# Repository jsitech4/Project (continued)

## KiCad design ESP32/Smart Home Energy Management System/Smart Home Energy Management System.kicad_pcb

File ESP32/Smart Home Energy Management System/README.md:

# Smart Home Energy Management System
Generated using KiCad Industrial Setup Script

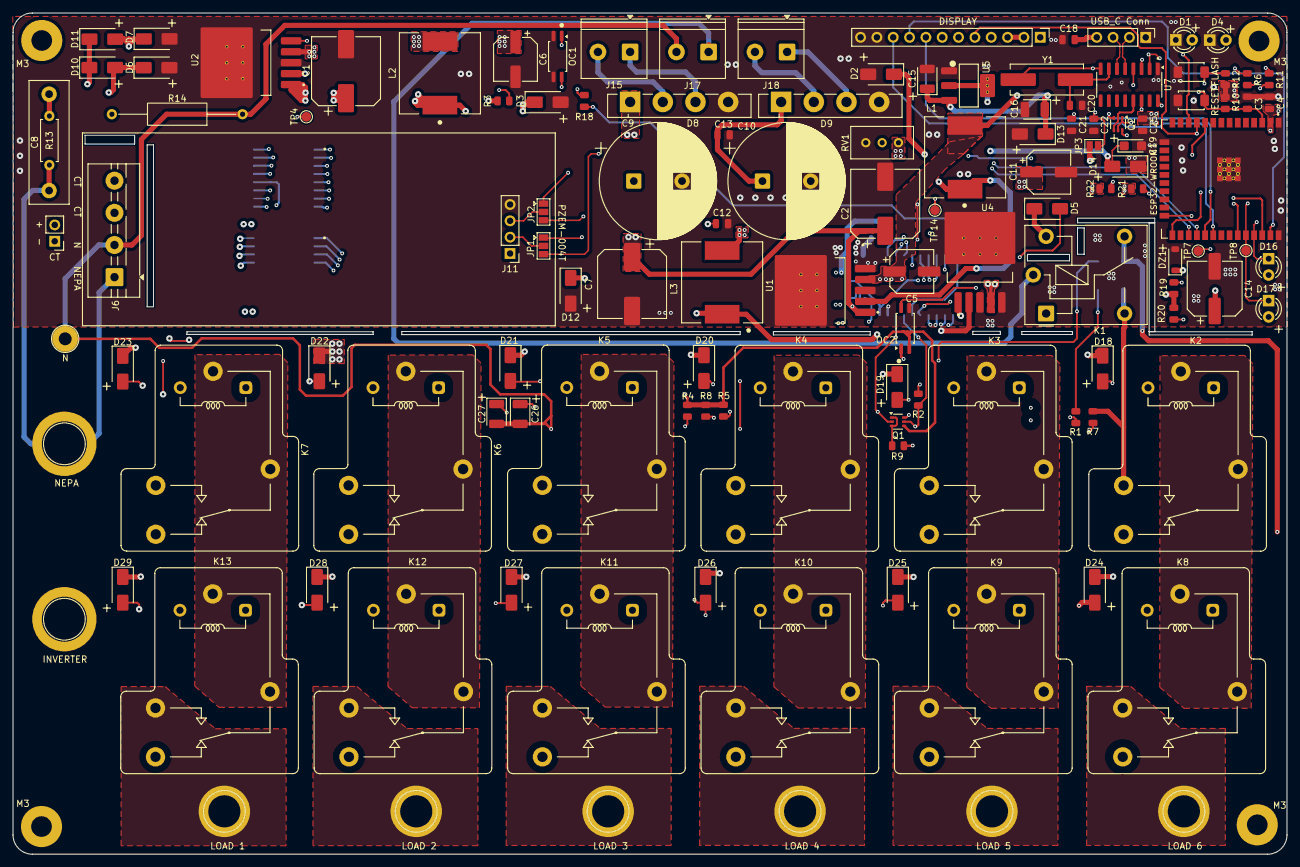
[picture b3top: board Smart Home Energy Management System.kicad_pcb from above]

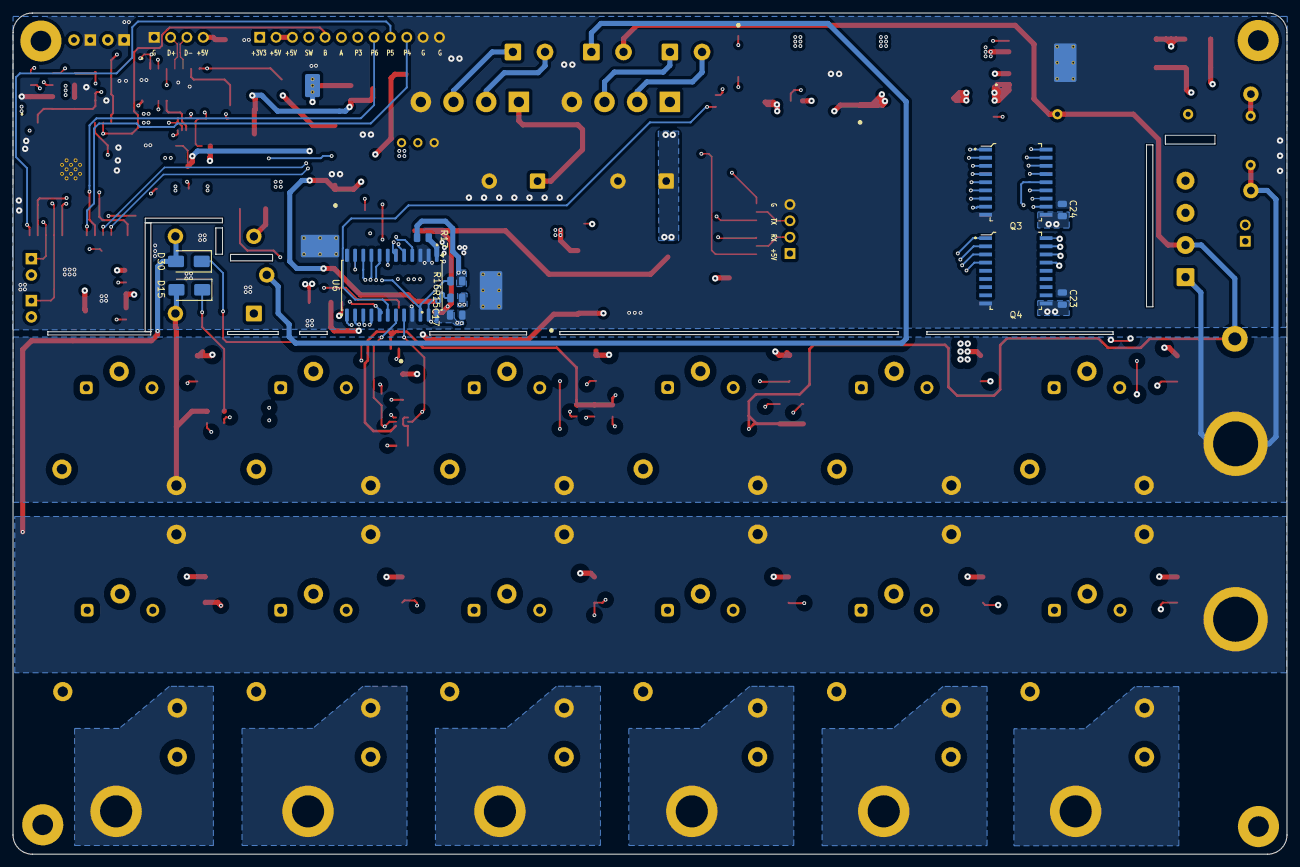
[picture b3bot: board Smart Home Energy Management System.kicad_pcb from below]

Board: 4 copper layers, 198.1 x 130.8 mm, 137 parts (11 on the bottom side), 102 nets.

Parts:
C1, C2, C7: 680uF_35V; CP_Elec_10x12.5
C3: 470nF; C_0805
C4, C12, C13, C18, C22, C23, C24, C25: 100nF; C_0805
C5, C6, C11: 220uF_16V; CP_Elec_6.3x7.7
C8: 145J400V; C_Rect_L19.0mm_W6.0mm_P15.00mm_MKS4
C9, C10: 2200uF/35V; CP_Radial_D18.0mm_P7.50mm
C14: 470uF/25V; CP_Elec_8x11.9
C15: 4.7uF/16V; C_CASE-B-3528-21(mm)
C16, C26, C27: 10uF_16V; C_CASE-B-3528-21(mm)
C17: 0.1uF/25V; C_0805
C19: 4.7uF/16V; CP_EIA-3216-18_Kemet-A
C20, C21: 22pF; C_0805
D1: Blue; LED_D3.0mm
D2, D3, D12: 1N5824; D_SMA
D4: GREEN; LED_D3.0mm
D5, D6, D7, D10, D11, D18, D19, D20, D21, D22, D23, D24, D25, D26, D27, D28, D29: SM4001; D_SMA
D8, D9: GBU8M; Diode_Bridge_Vishay_GBU
D13, D14: 1N5819; D_SMA
D15, D30: SM4007PL; D_SMA
D16: Red; LED_D3.0mm
D17: Green; LED_D3.0mm
DZ1: CMZ12; D_SOD-123
J1: NEPA; TestPoint_Plated_Hole_D5.0mm
J2: INVERTER; TestPoint_Plated_Hole_D5.0mm
J3: CT; PinHeader_1x02_P2.54mm_Vertical
J6: PZEM_LOAD; TerminalBlock_MaiXu_MX126-5.0-04P_1x04_P5.00mm
J10: N; TestPoint_Plated_Hole_D5.0mm
J11: PZEM_SIG; PinHeader_1x04_P2.54mm_Vertical
J14: USB_C Conn; PinHeader_1x04_P2.54mm_Vertical
J15: TRANS 1-OUT; TerminalBlock_Phoenix_PT-1,5-2-5.0-H_1x02_P5.00mm_Horizontal
J17: TRANS-IN; TerminalBlock_Phoenix_PT-1,5-2-5.0-H_1x02_P5.00mm_Horizontal
J18: TRANS 2-OUT; TerminalBlock_Phoenix_PT-1,5-2-5.0-H_1x02_P5.00mm_Horizontal
J19: DISPLAY; PinHeader_1x12_P2.54mm_Vertical
J20: LOAD 6; TestPoint_Plated_Hole_D5.0mm
J21: LOAD 5; TestPoint_Plated_Hole_D5.0mm
J22: LOAD 4; TestPoint_Plated_Hole_D5.0mm
J23: LOAD 3; TestPoint_Plated_Hole_D5.0mm
J24: LOAD 2; TestPoint_Plated_Hole_D5.0mm
J25: LOAD 1; TestPoint_Plated_Hole_D5.0mm
JP1, JP2: SolderJumper-3_P1.3mm_Open_Pad1.0x1.5mm
JP3: SolderJumper-2_P1.3mm_Open_Pad1.0x1.5mm
K1: 10A RELAY; Relay_SPDT_Finder_36.11
K2, K3, K4, K5, K6, K7, K8, K9, K10, K11, K12, K13: 30A RELAY; Relay_SPDT_RAYEX-L90
L1, L2, L3: 33uH; L_12x12mm_H6mm
OC1, OC2: PC817XFP; SOP-4_4.4x2.6mm_P1.27mm
Q1, Q2: UMH3N; SOT-363_SC-70-6
Q3, Q4: ULN2803ADWR; SOIC-18_W7.5mm
R1, R2, R7: 680k; R_0805
R3: 100k; R_0805
R4, R5, R8: 6.8k; R_0805
R6, R9, R11, R19, R20: 330R; R_0805
R10, R12, R15, R16, R17, R21, R22: 10k; R_0805
R13: 1M; R_Axial_DIN0207_L6.3mm_D2.5mm_P7.62mm_Horizontal
R14: 330R/2W; R_Axial_DIN0309_L9.0mm_D3.2mm_P20.32mm_Horizontal
R18: 150R; R_0805
RV1: 10K; Potentiometer_Bourns_3296W_Vertical
SW1: RESET; SW_TS-1088-AR02016
SW2: FLASH; SW_TS-1088-AR02016
TP4, TP7, TP8, TP14: TestPoint; TestPoint_Pad_D1.5mm
U1: LM2596S-3.3V; TO-263-5_L10.2-W8.9-P1.70-TL
U2: LM2596S-12; TO-263-5_L10.2-W8.9-P1.70-TL
U3: ESP32-WROOM; ESP32-WROOM-32E
U4: LM2596S-5V; TO-263-5_L10.2-W8.9-P1.70-TL
U5: AMS1117-3.3; SOT-223-3_L6.5-W3.4-P2.30-LS7.0-BR
U6: PCA9555D; SOIC-24W_7.5x15.4mm_P1.27mm
U7: CH340C; SOIC-16_3.9x9.9mm_P1.27mm
Y1: 12MHz; CRYSTAL-SMD_L11.5-W4.8-LS12.7

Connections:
+3.3V: C4.2, C5.1, C17.1, C25.2, D14.1 (K), J19.1, JP3.2 (B), L1.2, R10.2, R12.2, R15.2, R16.2, R17.2, R19.1, R20.1, R21.2, R22.1, U1.4 (FB), U3.2 (VDD), U6.24 (VDD), U7.16 (VCC)
+5V: C11.1, J11.1, J19.2, J19.3, L3.2, RV1.3, U4.4 (FB)
+12V: C6.1, C23.1, C24.1, D18.1 (K), D19.1 (K), D20.1 (K), D21.1 (K), D22.1 (K), D23.1 (K), D24.1 (K), D25.1 (K), D26.1 (K), D27.1 (K), D28.1 (K), D29.1 (K), K2.A1, K3.A1, K4.A1, K5.A1, K6.A1, K7.A1, K8.A2, K9.A2, K10.A2, K11.A2, K12.A2, K13.A2, L2.2, Q3.10 (COM), Q4.10 (COM), U2.4 (FB)
/1TR 1: D8.3, J15.1
/1TR 2: D8.2, J15.2
/2TR 1: D9.3, J18.1
/2TR 2: D9.2, J18.2
/12V_EN: OC1.1, R18.1
/CONST: J19.7, RV1.2
/CT +: J3.2, J6.4
/CT -: J3.1, J6.3
/D+: J14.2, U7.5 (UD+)
/D-: J14.3, U7.6 (UD-)
/DTR: Q2.2 (B1), Q2.4 (E2), U7.13 (~DTR)
/EN: C3.2, Q2.6 (C1), R10.1, SW1.2, U3.3 (EN)
/GPIO0: Q2.3 (C2), R12.1, SW2.2, U3.25 (IOA0)
/GPIO1/TX: D16.1 (K), JP1.1 (A), TP7.1, U3.35 (TXD0/IO1), U7.3 (RXD)
/GPIO2: R11.1, U3.24 (IOA2)
/GPIO3/RX: D17.1 (K), JP2.3 (C), TP8.1, U3.34 (RXD0/IO3), U7.2 (TXD)
/GPIO5/CS: J19.8, U3.29 (IO5)
/GPIO16: JP2.1 (A), U3.27 (IO16)
/GPIO17: JP1.3 (C), U3.28 (IO17)
/GPIO18/SCK: J19.10, U3.30 (IO18)
/GPIO21/SDA: R15.1, U3.33 (IO21), U6.23 (SDA)
/GPIO22/SCL: R16.1, TP14.1, U3.36 (IO22), U6.22 (SCL)
/GPIO23/MOSI: J19.9, U3.37 (IO23)
/GPIO25: J19.6, R22.2, U3.10 (IOA25)
/GPIO26: J19.5, R21.1, U3.11 (IOA26)
/GPIO27: J19.4, U3.12 (IOA27)
/IND_LED: R6.1, U6.17 (IO1_4)
/INVERTER: D30.2 (A), J2.1, K1.12, K2.12, K3.12, K4.12, K5.12, K6.12, K7.12
/INVERTER_SENSE: C27.1, Q1.5 (B2), R2.1, R4.2, U6.19 (IO1_6)
/LOAD1: J25.1, K13.14
/LOAD2: J24.1, K12.14
/LOAD3: J23.1, K11.14
/LOAD4: J22.1, K10.14
/LOAD5: J21.1, K9.14
/LOAD6: J20.1, K8.14
/N: C26.2, C27.2, J6.2, J10.1, J17.2, OC2.2, Q1.4 (E2), R4.1, R5.1, R8.1, R14.1
/NEPA: C8.2, D15.2 (A), J1.1, J6.1, K1.14, K2.14, K3.14, K4.14, K5.14, K6.14, K7.14, R7.2, R13.2
/NEPA_SENSE: C26.1, Q1.2 (B1), R1.1, R5.2, U6.20 (IO1_7)
/RD1C1: D24.2 (A), K8.A1, Q3.18 (OUT1)
/RD1C2: D18.2 (A), K2.A2, Q3.17 (OUT2)
/RD1C3: D25.2 (A), K9.A1, Q3.16 (OUT3)
/RD1C4: D19.2 (A), K3.A2, Q3.15 (OUT4)
/RD1C5: D26.2 (A), K10.A1, Q3.14 (OUT5)
/RD1C6: D20.2 (A), K4.A2, Q3.13 (OUT6)
/RD1C7: D27.2 (A), K11.A1, Q3.12 (OUT7)
/RD1C8: D21.2 (A), K5.A2, Q3.11 (OUT8)
/RD2C1: D28.2 (A), K12.A1, Q4.18 (OUT1)
/RD2C2: D22.2 (A), K6.A2, Q4.17 (OUT2)
/RD2C3: D29.2 (A), K13.A1, Q4.16 (OUT3)
/RD2C4: D23.2 (A), K7.A2, Q4.15 (OUT4)
/RTS: Q2.1 (E1), Q2.5 (B2), U7.14 (~RTS)
/SELECT1: K7.11A, K7.11B, K13.11A, K13.11B
/SELECT2: K6.11A, K6.11B, K12.11A, K12.11B
/SELECT3: K5.11A, K5.11B, K11.11A, K11.11B
/SELECT4: K4.11A, K4.11B, K10.11A, K10.11B
/SELECT5: K3.11A, K3.11B, K9.11A, K9.11B
/SELECT6: K2.11A, K2.11B, K8.11A, K8.11B
/TRANS-IN: J17.1, K1.11
/~INT: R17.1, U6.1 (~INT)
GND: C1.2, C2.2, C3.1, C4.1, C5.2, C6.2, C7.2, C9.2, C10.2, C11.2, C12.1, C13.1, C14.2, C15.2, C16.2, C17.2, C18.1, C19.2, C20.2, C21.2, C22.1, C23.2, C24.2, C25.1, D1.1 (K), D2.2 (A), D3.2 (A), D4.1 (K), D6.2 (A), D7.2 (A), D8.4 (-), D9.4 (-), D12.2 (A), D13.2 (A), DZ1.2 (A), J11.4, J14.1, J19.11, J19.12, OC1.2, OC1.3, OC2.3, Q3.9 (GND), Q4.9 (GND), RV1.1, SW1.1, SW2.1, U1.3 (GND), U1.5 (~ON/OFF), U1.6 (GND), U2.3 (GND), U2.6 (GND), U3.1 (GND), U3.15 (GND), U3.38 (GND), U3.39 (GND), U4.3 (GND), U4.5 (~ON/OFF), U4.6 (GND), U5.1 (GND), U6.2 (A1), U6.3 (A2), U6.12 (VSS), U6.21 (A0), U7.1 (GND)
unnamed: D1.2 (A), R6.2
unnamed: D2.1 (K), L1.1, U1.2 (OUT)
unnamed: D3.1 (K), L2.1, U2.2 (OUT)
unnamed: D4.2 (A), R11.2
unnamed: D5.2 (A), K1.A1, OC2.4
unnamed: C8.1, D6.1 (K), D10.2 (A), R13.1
unnamed: D7.1 (K), D11.2 (A), R14.2
unnamed: D12.1 (K), L3.1, U4.2 (OUT)
unnamed: C15.1, C16.1, C18.2, D13.1 (K), J14.4, U5.3 (VI)
unnamed: C19.1, D14.2 (A), U5.2 (VO), U5.4 (VO)
unnamed: D15.1 (K), R1.2
unnamed: D16.2 (A), R19.2
unnamed: D17.2 (A), R20.2
unnamed: D30.1 (K), R2.2
unnamed: J11.2, JP1.2 (B)
unnamed: J11.3, JP2.2 (B)
unnamed: C22.2, JP3.1 (A), U7.4 (V3)
unnamed: OC2.1, R9.2
unnamed: Q1.6 (C1), R7.1, R8.2
unnamed: Q1.1 (E1), Q1.3 (C2), R9.1
unnamed: Q3.1 (IN1), U6.4 (IO0_0)
unnamed: Q3.2 (IN2), U6.5 (IO0_1)
unnamed: Q3.3 (IN3), U6.6 (IO0_2)
unnamed: Q3.4 (IN4), U6.7 (IO0_3)
unnamed: Q3.5 (IN5), U6.8 (IO0_4)
unnamed: Q3.6 (IN6), U6.9 (IO0_5)
unnamed: Q3.7 (IN7), U6.10 (IO0_6)
unnamed: Q3.8 (IN8), U6.11 (IO0_7)
unnamed: Q4.1 (IN1), U6.13 (IO1_0)
unnamed: Q4.2 (IN2), U6.14 (IO1_1)
unnamed: Q4.3 (IN3), U6.15 (IO1_2)
unnamed: Q4.4 (IN4), U6.16 (IO1_3)
unnamed: OC1.4, R3.1, TP4.1, U2.5 (~ON/OFF)
unnamed: R18.2, U6.18 (IO1_5)
unnamed: C20.1, U7.7 (Xi), Y1.2
unnamed: C21.1, U7.8 (Xo), Y1.1
VCC1: C2.1, C7.1, C9.1, C12.2, D8.1 (+), U1.1 (VIN), U4.1 (VIN)
VCC2: C1.1, C10.1, C13.2, D9.1 (+), R3.2, U2.1 (VIN)
VCC3: C14.1, D5.1 (K), D10.1 (K), D11.1 (K), DZ1.1 (K), K1.A2

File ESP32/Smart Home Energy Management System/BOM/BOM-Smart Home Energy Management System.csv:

Comment,Designator,Footprint,LCSC,Quantity
ESP32,U3,ESP32-WROOM-32E,,1
LM2596S-12,U2,TO-263-5_L10.2-W8.9-P1.70-TL,,1
LM2596S-3.3V,U1,TO-263-5_L10.2-W8.9-P1.70-TL,,1
LM2596S-5V,U4,TO-263-5_L10.2-W8.9-P1.70-TL,,1
PCA9555D,U6,SOIC-24W_7.5x15.4mm_P1.27mm,,1
CH340C,U7,SOIC-16_3.9x9.9mm_P1.27mm,,1
ULN2803ADWR,Q4,SOIC-18_W7.5mm,,1
ULN2803ADWR,Q3,SOIC-18_W7.5mm,,1
680uF_35V,C1,CP_Elec_10x12.5,,1
6.8k,R5,R_0805,,1
Green,D17,LED_D3.0mm,,1
330R,R19,R_0805,,1
22pF,C21,C_0805,,1
GREEN,D4,LED_D3.0mm,,1
22pF,C20,C_0805,,1
470uF/25V,C14,CP_Elec_8x11.9,,1
4.7uF/16V,C15,C_CASE-B-3528-21(mm),,1
100nF,C4,C_0805,,1
100nF,C13,C_0805,,1
680k,R1,R_0805,,1
UMH3N,Q2,SOT-363_SC-70-6,,1
4.7uF/16V,C19,CP_EIA-3216-18_Kemet-A,,1
SM4001,D6,D_SMA,,1
145J400V,C8,C_Rect_L19.0mm_W6.0mm_P15.00mm_MKS4,,1
10uF_16V,C27,C_CASE-B-3528-21(mm),,1
PC817XFP,OC2,SOP-4_4.4x2.6mm_P1.27mm,,1
PC817XFP,OC1,SOP-4_4.4x2.6mm_P1.27mm,,1
150R,R18,R_0805,,1
SM4001,D20,D_SMA,,1
1N5824,D2,D_SMA,,1
330R,R20,R_0805,,1
330R/2W,R14,R_Axial_DIN0309_L9.0mm_D3.2mm_P20.32mm_Horizontal,,1
1N5819,D14,D_SMA,,1
SM4001,D29,D_SMA,,1
470nF,C3,C_0805,,1
10uF_16V,C26,C_CASE-B-3528-21(mm),,1
SM4001,D10,D_SMA,,1
SM4001,D23,D_SMA,,1
330R,R11,R_0805,,1
SM4001,D18,D_SMA,,1
SM4001,D21,D_SMA,,1
Blue,D1,LED_D3.0mm,,1
SM4001,D26,D_SMA,,1
33uH,L2,L_12x12mm_H6mm,,1
100nF,C25,C_0805,,1
SM4001,D24,D_SMA,,1
220uF_16V,C11,CP_Elec_6.3x7.7,,1
GBU8M,D9,Diode_Bridge_Vishay_GBU,,1
2200uF/35V,C9,CP_Radial_D18.0mm_P7.50mm,,1
SM4001,D19,D_SMA,,1
SM4001,D11,D_SMA,,1
1N5824,D12,D_SMA,,1
SM4001,D28,D_SMA,,1
6.8k,R4,R_0805,,1
SM4001,D25,D_SMA,,1
6.8k,R8,R_0805,,1
SM4001,D22,D_SMA,,1
330R,R9,R_0805,,1
100nF,C22,C_0805,,1
680uF_35V,C7,CP_Elec_10x12.5,,1
FLASH,SW2,SW_TS-1088-AR02016,,1
680uF_35V,C2,CP_Elec_10x12.5,,1
10K,RV1,Potentiometer_Bourns_3296W_Vertical,,1
680k,R7,R_0805,,1
10k,R10,R_0805,,1
10k,R21,R_0805,,1
RESET,SW1,SW_TS-1088-AR02016,,1
100nF,C12,C_0805,,1
10k,R12,R_0805,,1
220uF_16V,C5,CP_Elec_6.3x7.7,,1
33uH,L1,L_12x12mm_H6mm,,1
GBU8M,D8,Diode_Bridge_Vishay_GBU,,1
100nF,C18,C_0805,,1
1N5819,D13,D_SMA,,1
100k,R3,R_0805,,1
SM4001,D27,D_SMA,,1
UMH3N,Q1,SOT-363_SC-70-6,,1
220uF_16V,C6,CP_Elec_6.3x7.7,,1
680k,R2,R_0805,,1
Red,D16,LED_D3.0mm,,1
CMZ12,DZ1,D_SOD-123,,1
SM4001,D5,D_SMA,,1
1N5824,D3,D_SMA,,1
10uF_16V,C16,C_CASE-B-3528-21(mm),,1
AMS1117-3.3,U5,SOT-223-3_L6.5-W3.4-P2.30-LS7.0-BR,,1
12MHz,Y1,CRYSTAL-SMD_L11.5-W4.8-LS12.7,,1
2200uF/35V,C10,CP_Radial_D18.0mm_P7.50mm,,1
SM4001,D7,D_SMA,,1
330R,R6,R_0805,,1
10k,R22,R_0805,,1
1M,R13,R_Axial_DIN0207_L6.3mm_D2.5mm_P7.62mm_Horizontal,,1
0.1uF/25V,C17,C_0805,,1
100nF,C23,C_0805,,1
10k,R15,R_0805,,1
SM4007PL,D30,D_SMA,,1
10k,R16,R_0805,,1
10k,R17,R_0805,,1
SM4007PL,D15,D_SMA,,1
100nF,C24,C_0805,,1
33uH,L3,L_12x12mm_H6mm,,1

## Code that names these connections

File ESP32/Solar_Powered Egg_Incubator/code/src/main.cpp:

#include <Arduino.h>
#include <Wire.h>
#include "Pins.h"
#include "battery_level/battery_level.h"
#include "solar_level/solar_level.h"
#include "ultrasonic/ultrasonic.h"
#include "rotary_encoder/rotary_encoder.h"
#include "buzzer/buzzer.h"
#include "heater/heater.h"
#include "spinner/spinner.h"
#include "humidifier/humidifier.h"
#include "temp_hum/temp_hum.h"
#include "rtc_clock/rtc_clock.h"
#include "lcd_screen/lcd_screen.h"
#include "wifi_manager/wifi_manager.h"
#include "web_dashboard/web_dashboard.h"
#include "sleep_wake/sleep_wake.h"
#include "error_handling/error_handling.h"
#include "reset/reset.h"

static unsigned long lastPrint = 0;

void setup()
{
  Serial.begin(115200);
  Pins::begin();
  Wire.begin(Pins::I2C_SDA, Pins::I2C_SCL);
  battery_level::begin(Pins::BATTERY_LEVEL, 2.0f);
  solar_level::begin(Pins::SOLAR_LEVEL, 4.0f);
  ultrasonic::begin(Pins::ULTRASONIC_TRIG, Pins::ULTRASONIC_ECHO);
  rotary_encoder::begin(Pins::ENCODER_A, Pins::ENCODER_B, Pins::ENCODER_SW);
  buzzer::begin(Pins::BUZZER);
  heater::begin(Pins::HEATER_RELAY, true);
  spinner::begin(Pins::SPINNER_RELAY, true);
  humidifier::begin(Pins::HUMIDIFIER_RELAY, true);
  temp_hum::begin();
  rtc_clock::begin();
  lcd_screen::begin();
  wifi_manager::begin();
  web_dashboard::begin();
  sleep_wake::begin();
  error_handling::begin();
  reset::begin();
  Serial.println("Solar Powered Egg Incubator Ready");
  Serial.println("Connect to WiFi AP: Egg_Incubator");
  Serial.println("Password: 12345678");
  Serial.println("Dashboard: http://192.168.4.1");
}

void loop()
{
  battery_level::update();
  solar_level::update();
  ultrasonic::update();
  rotary_encoder::update();
  buzzer::update();
  heater::update();
  spinner::update();
  humidifier::update();
  temp_hum::update();
  rtc_clock::update();
  lcd_screen::update();
  wifi_manager::update();
  web_dashboard::update();
  sleep_wake::update();
  error_handling::update();
  reset::update();

  if (rotary_encoder::wasPressed())
    buzzer::beep(60, 60, 1);
}

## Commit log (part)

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2025-10-06 🚀 Initial KiCad structure setup
2025-10-06 Start
2025-10-06 Update from work
2025-10-07 update from home
2025-10-07 update from work(Schematic done)
2025-11-03 Changing Blind/Buried Via into Through-hole type
2026-06-10 Updated project files
